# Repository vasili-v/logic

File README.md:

# Logic

## About

The repository contains a set of schematics for a variety of PMOS logic gates.

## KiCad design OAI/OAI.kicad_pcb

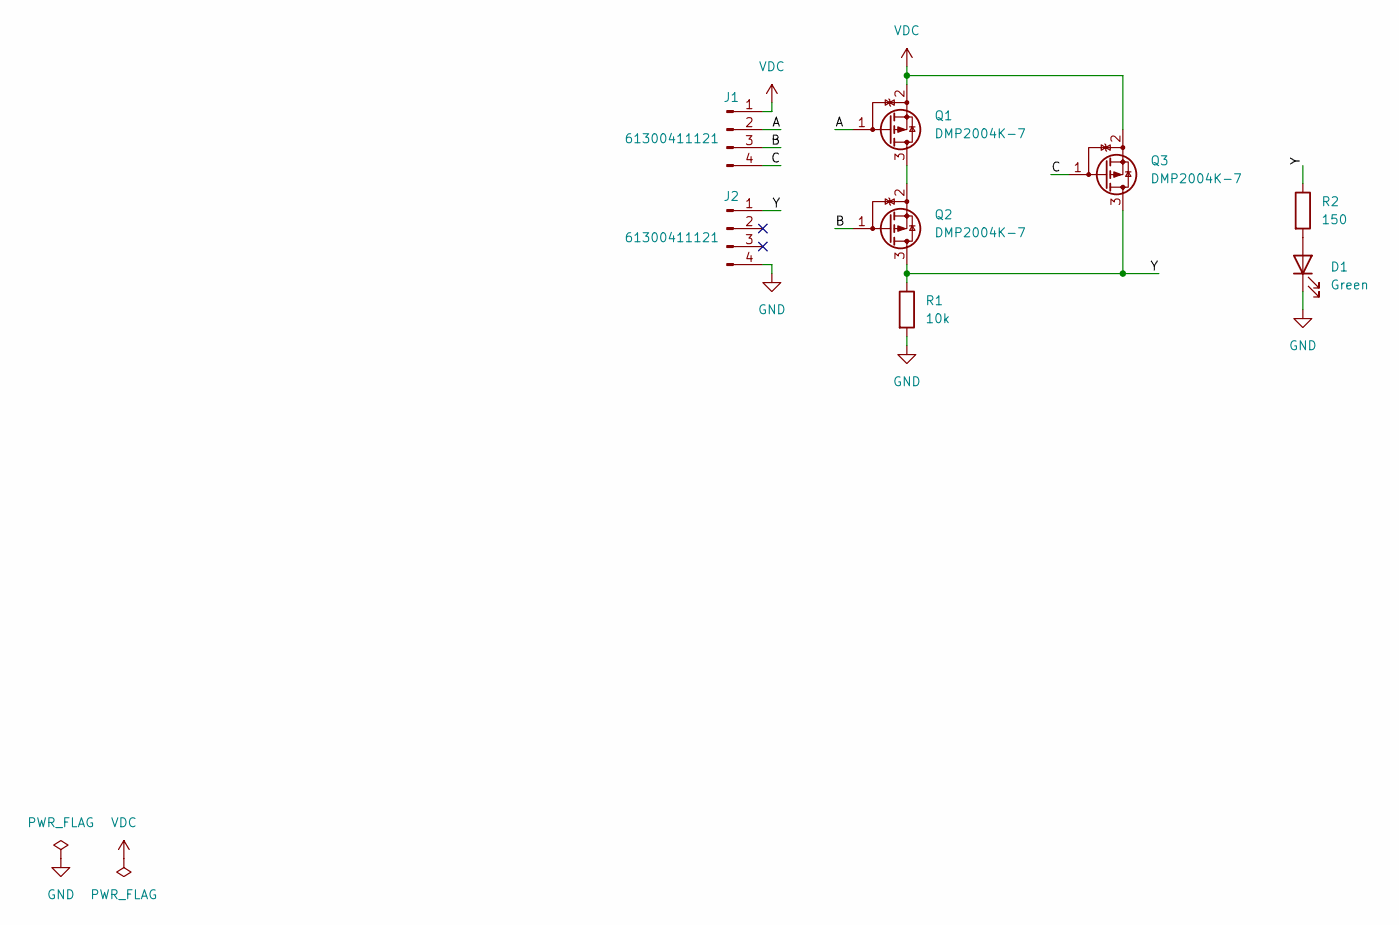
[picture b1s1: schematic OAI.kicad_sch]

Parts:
D1: Green; LED_0603_1608Metric
J1: 61300411121; PinHeader_1x04_P2.54mm_Vertical_Top
J2: 61300411121; PinHeader_1x04_P2.54mm_Vertical_Bottom
Q1, Q2, Q3: DMP2004K-7; SOT-23
R1: 10k; R_0603_1608Metric
R2: 150; R_0603_1608Metric

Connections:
/A: J1.2, Q1.1 (G)
/B: J1.3, Q2.1 (G)
/C: J1.4, Q3.1 (G)
/Y: J2.1, Q2.3 (D), Q3.3 (D), R1.1, R2.1
GND: D1.1 (K), J2.4, R1.2
unnamed: D1.2 (A), R2.2
unnamed: Q1.3 (D), Q2.2 (S)
VDC: J1.1, Q1.2 (S), Q3.2 (S)

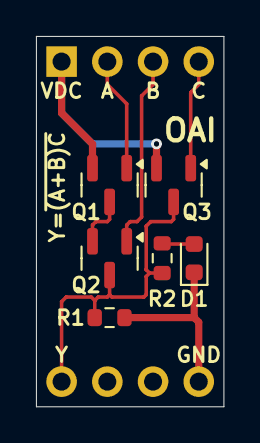
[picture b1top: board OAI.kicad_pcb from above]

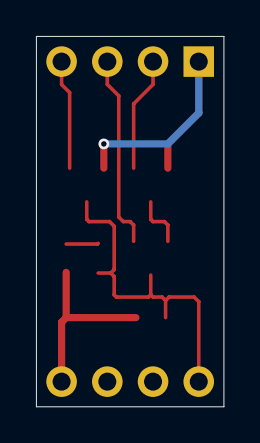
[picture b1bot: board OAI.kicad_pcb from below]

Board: 2 copper layers, 10.4 x 20.6 mm, 8 parts (2 on the bottom side), 8 nets.

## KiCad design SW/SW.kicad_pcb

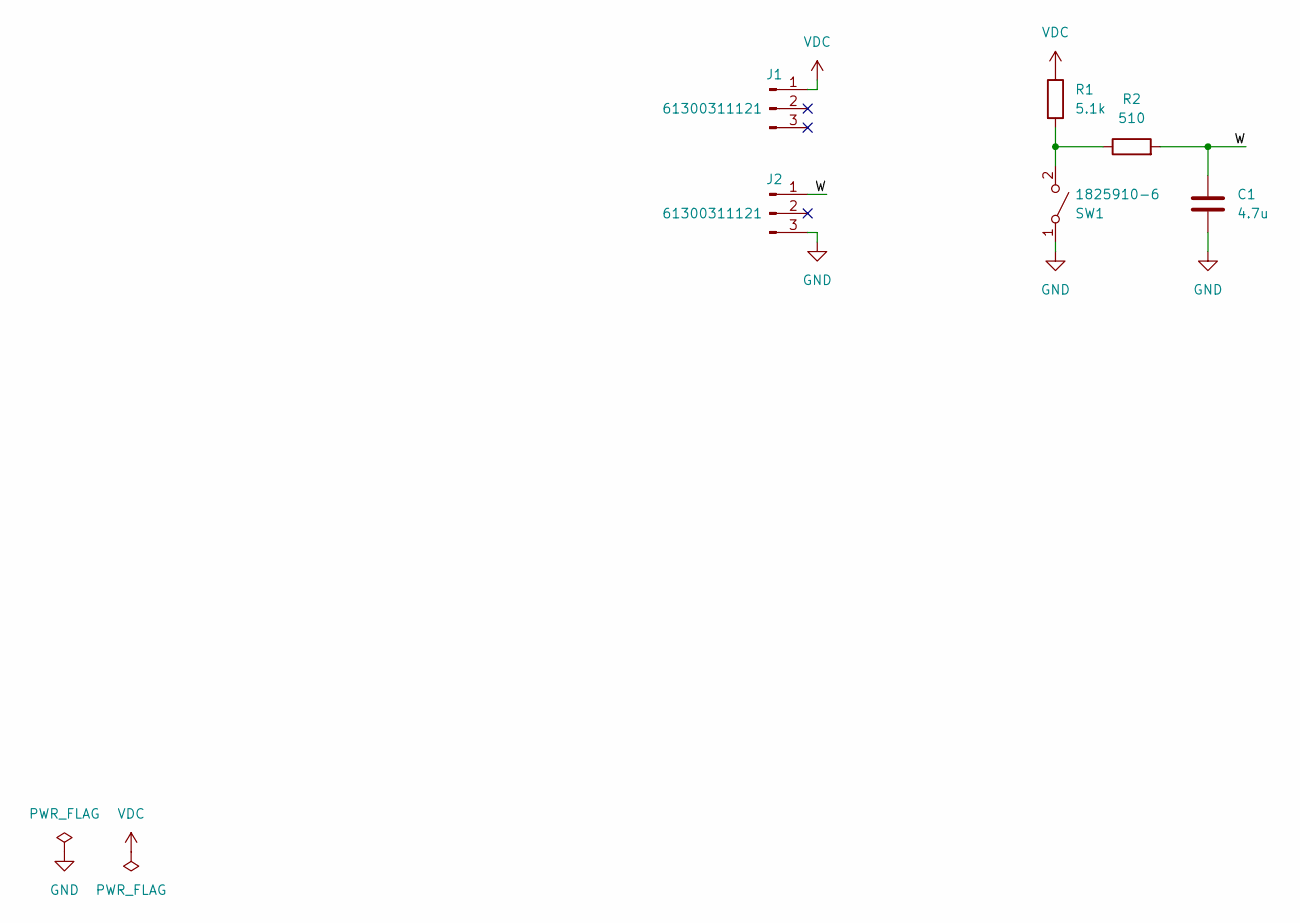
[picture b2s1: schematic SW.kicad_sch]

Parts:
C1: 4.7u; C_0603_1608Metric
J1: 61300311121; PinHeader_1x03_P2.54mm_Vertical_Top
J2: 61300311121; PinHeader_1x03_P2.54mm_Vertical_Bottom
R1: 5.1k; R_0603_1608Metric
R2: 510; R_0603_1608Metric
SW1: 1825910-6; SW_DIP_SPSTx01_Slide_9.78x4.72mm_W7.62mm_P2.54mm

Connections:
/W: C1.1, J2.1, R2.2
GND: C1.2, J2.3, SW1.1 (A)
unnamed: R1.2, R2.1, SW1.2 (B)
VDC: J1.1, R1.1

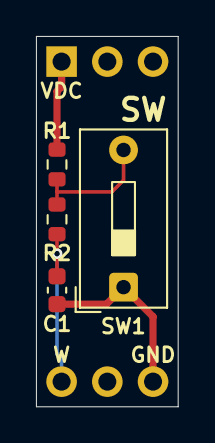
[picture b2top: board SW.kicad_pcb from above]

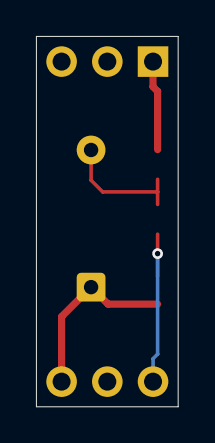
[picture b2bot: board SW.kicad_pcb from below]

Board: 2 copper layers, 7.9 x 20.6 mm, 6 parts (2 on the bottom side), 4 nets.

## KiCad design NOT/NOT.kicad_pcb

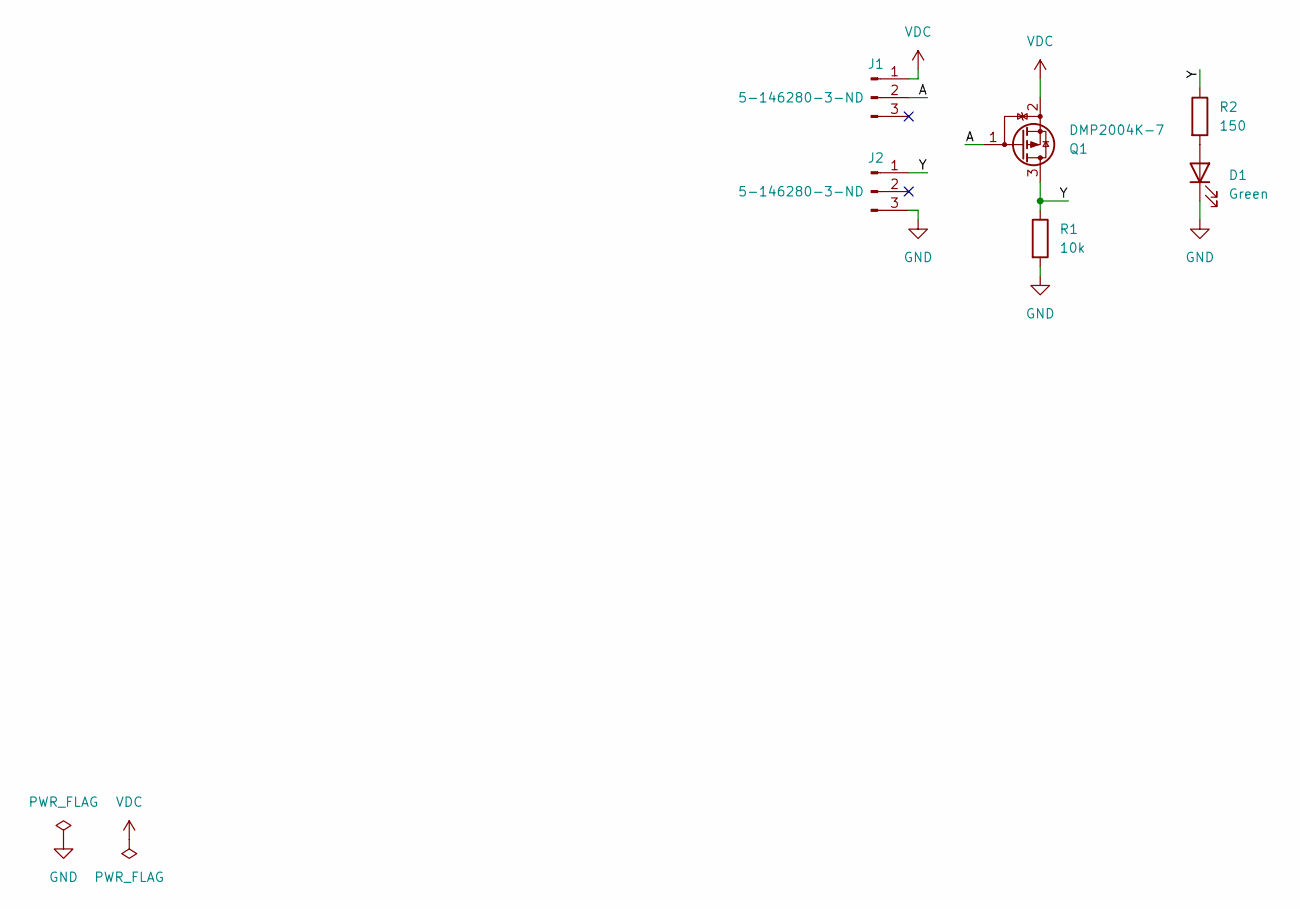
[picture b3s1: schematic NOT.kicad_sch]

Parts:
D1: Green; LED_0603_1608Metric
J1: 5-146280-3-ND; PinHeader_1x03_P2.54mm_Vertical_Top
J2: 5-146280-3-ND; PinHeader_1x03_P2.54mm_Vertical_Bottom
Q1: DMP2004K-7; SOT-23
R1: 10k; R_0603_1608Metric
R2: 150; R_0603_1608Metric

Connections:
/A: J1.2, Q1.1 (G)
/Y: J2.1, Q1.3 (D), R1.1, R2.1
GND: D1.1 (K), J2.3, R1.2
unnamed: D1.2 (A), R2.2
VDC: J1.1, Q1.2 (S)

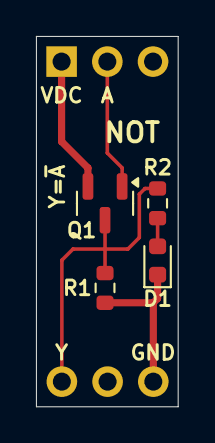
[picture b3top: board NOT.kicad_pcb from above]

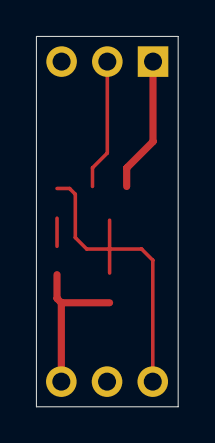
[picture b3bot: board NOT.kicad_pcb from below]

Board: 2 copper layers, 7.9 x 20.6 mm, 6 parts (2 on the bottom side), 5 nets.

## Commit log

2025-03-29 Add NAND and partially NOR gates schematics
2025-03-30 Finish NOR gate PCB and unify NAND with it
2025-04-02 Change pull-down resistor to 0.1w
2025-04-10 Add SW debounce simulation
2025-04-10 Add SWitch schematic
2025-04-10 Add PUSH button schematic
2025-04-10 Add NOT gate schematic
2025-04-12 Add OAI gate schematic
2025-04-12 Generate fabrication files
